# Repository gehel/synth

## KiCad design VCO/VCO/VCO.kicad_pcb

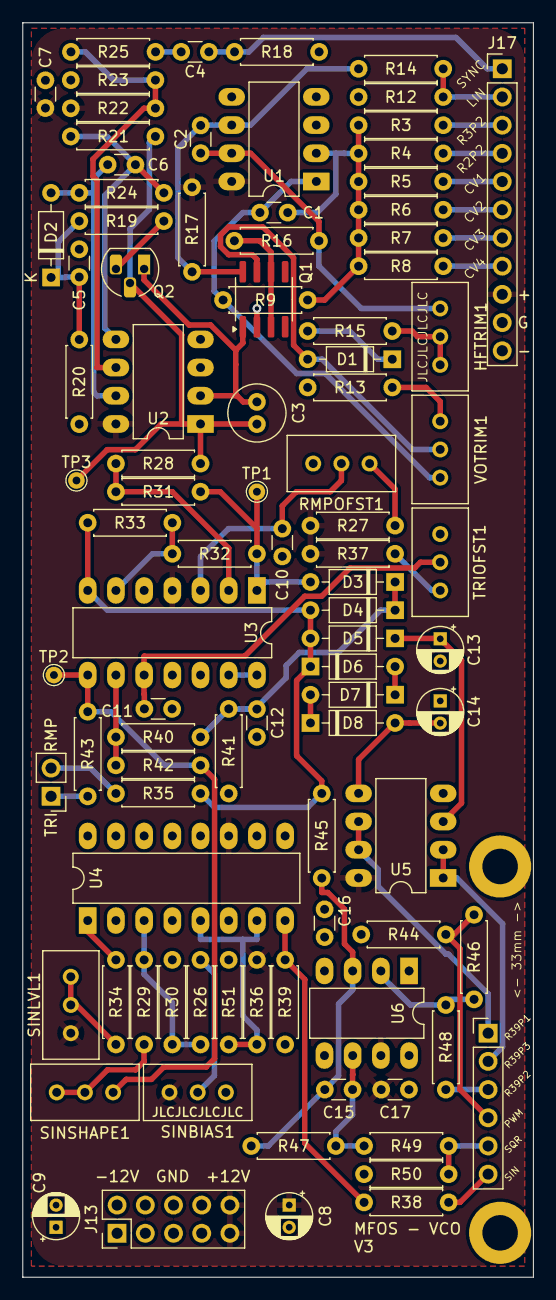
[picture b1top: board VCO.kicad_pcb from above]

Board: 4 copper layers, 46.0 x 113.0 mm, 96 parts (0 on the bottom side), 62 nets.

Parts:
C1, C2, C5: 100pF; C_Disc_D3.0mm_W1.6mm_P2.50mm
C3: 5nF; C_Radial_D5.0mm_H11.0mm_P2.00mm
C4: 1nF; C_Disc_D3.0mm_W1.6mm_P2.50mm
C6: 4.7pF; C_Disc_D3.0mm_W1.6mm_P2.50mm
C7, C10, C11, C16, C17: 100nF; C_Disc_D3.0mm_W1.6mm_P2.50mm
C8, C9: 10uF; CP_Radial_D4.0mm_P2.00mm
C12: 2nF; C_Disc_D3.0mm_W1.6mm_P2.50mm
C13, C14: 1uF; CP_Radial_D4.0mm_P2.00mm
C15: 10pF; C_Disc_D3.0mm_W1.6mm_P2.50mm
D1, D2, D3, D4, D5, D6, D7, D8: 1N914; D_DO-35_SOD27_P7.62mm_Horizontal
H1, H2: MountingHole_Pad; MountingHole_3.2mm_M3_DIN965_Pad
HFTRIM1: 100K; Potentiometer_Bourns_3296W_Vertical
J13: Conn_02x05_Odd_Even; PinHeader_2x05_P2.54mm_Vertical
J15: Conn_01x06; PinHeader_1x06_P2.54mm_Vertical
J17: Conn_01x11; PinHeader_1x11_P2.54mm_Vertical
J19: Conn_01x02; PinHeader_1x02_P2.54mm_Vertical
Q1: SSM2210; SOIC-8_3.9x4.9mm_P1.27mm
Q2: PN4391; TO-92L_HandSolder
R3, R14, R17, R24, R36: 1M; R_Axial_DIN0207_L6.3mm_D2.5mm_P7.62mm_Horizontal
R4, R5, R6, R7, R8, R12, R18, R19, R27, R34, R44, R45: 100K; R_Axial_DIN0207_L6.3mm_D2.5mm_P7.62mm_Horizontal
R9, R23: 2K; R_Axial_DIN0207_L6.3mm_D2.5mm_P7.62mm_Horizontal
R13: 475R; R_Axial_DIN0207_L6.3mm_D2.5mm_P7.62mm_Horizontal
R15, R39, R49: 4.7K; R_Axial_DIN0207_L6.3mm_D2.5mm_P7.62mm_Horizontal
R16, R21, R22, R28, R32, R33, R37, R40, R46, R48: 10K; R_Axial_DIN0207_L6.3mm_D2.5mm_P7.62mm_Horizontal
R20: 18K; R_Axial_DIN0207_L6.3mm_D2.5mm_P7.62mm_Horizontal
R25, R30, R35, R38, R43: 1K; R_Axial_DIN0207_L6.3mm_D2.5mm_P7.62mm_Horizontal
R26: 470K; R_Axial_DIN0207_L6.3mm_D2.5mm_P7.62mm_Horizontal
R29, R41, R42: 20K; R_Axial_DIN0207_L6.3mm_D2.5mm_P7.62mm_Horizontal
R31: 47K; R_Axial_DIN0207_L6.3mm_D2.5mm_P7.62mm_Horizontal
R47: 10M; R_Axial_DIN0207_L6.3mm_D2.5mm_P7.62mm_Horizontal
R50: 3K; R_Axial_DIN0207_L6.3mm_D2.5mm_P7.62mm_Horizontal
R51: 130K; R_Axial_DIN0207_L6.3mm_D2.5mm_P7.62mm_Horizontal
RMPOFST1: 10K; Potentiometer_Bourns_3296W_Vertical
SINBIAS1: 100K; Potentiometer_Bourns_3296W_Vertical
SINLVL1: 1M; Potentiometer_Bourns_3296W_Vertical
SINSHAPE1: 100K; Potentiometer_Bourns_3296W_Vertical
TP1, TP2, TP3: TestPoint; TestPoint_THTPad_D1.5mm_Drill0.7mm
TRIOFST1: 10K; Potentiometer_Bourns_3296W_Vertical
U1: OP275; DIP-8_W7.62mm_LongPads
U2, U5: TL072; DIP-8_W7.62mm_LongPads
U3: TL074; DIP-14_W7.62mm_LongPads
U4: LM13700; DIP-16_W7.62mm_LongPads
U6: TL071; DIP-8_W7.62mm_LongPads
VOTRIM1: 100R; Potentiometer_Bourns_3296W_Vertical

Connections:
+12V: C7.2, C8.1, C17.2, J13.9, J13.10, J17.9, R17.2, R22.2, R27.2, R36.1, R37.2, SINBIAS1.3, SINLVL1.3, U1.8 (V+), U2.8 (V+), U3.4 (V+), U4.11 (V+), U5.8 (V+), U6.7 (V+)
-12V: C9.2, C12.1, C16.2, J13.1, J13.2, J17.11, R20.1, R39.2, R41.2, SINBIAS1.1, U1.4 (V-), U2.4 (V-), U3.11 (V-), U4.6 (V-), U5.4 (V-), U6.4 (V-)
CV1: J17.5, R5.1
CV2: J17.6, R6.1
CV3: J17.7, R7.1
CV4: J17.8, R8.1
GND: C5.1, C7.1, C8.2, C9.1, C10.1, C11.1, C13.2, C14.1, C16.1, C17.1, H1.1, H2.1, J13.3, J13.4, J13.5, J13.6, J13.7, J13.8, J17.10, Q1.2 (B1), R12.1, R13.1, R18.1, R23.2, R30.2, R44.2, R50.2, R51.2, RMPOFST1.1, TRIOFST1.1, U1.3 (+), U1.5 (+), U2.3 (+), U3.5 (+), U3.12 (+), U4.4 (-), U4.13 (-), U4.14 (+)
LIN: J17.2, R12.2, R14.1
unnamed: C1.2, R9.2, U1.1, VOTRIM1.1
unnamed: C2.2, HFTRIM1.3, R16.2, U1.7
unnamed: C4.2, R25.1
unnamed: C15.1, R47.2, R49.1, U6.6
unnamed: D1.2 (A), Q1.7 (B2), VOTRIM1.2
unnamed: D1.1 (K), R15.1
unnamed: C6.2, D2.2 (A), R24.2, U2.7
unnamed: C5.2, D2.1 (K), R19.2, R20.2
unnamed: D3.2 (A), R31.2, R32.2, TP1.1, U3.1
unnamed: C12.2, D3.1 (K), D4.1 (K), R40.1, R41.1
unnamed: D4.2 (A), D5.2 (A), D6.1 (K), R33.2, R35.1, R45.1, U3.7
unnamed: C13.1, D5.1 (K), U5.3 (+)
unnamed: D6.2 (A), D7.1 (K)
unnamed: D7.2 (A), D8.1 (K)
unnamed: C14.2, D8.2 (A), U5.5 (+)
unnamed: HFTRIM1.1, HFTRIM1.2, R15.2
unnamed: C3.1, Q1.1 (C1), Q2.1 (D), U2.2 (-)
unnamed: Q1.3 (E1), Q1.6 (E2), R16.1
unnamed: C2.1, Q1.8 (C2), R14.2, R17.1, U1.6 (-)
unnamed: Q2.3 (G), R19.1
unnamed: R13.2, VOTRIM1.3
unnamed: R26.1, SINBIAS1.2
unnamed: R27.1, RMPOFST1.3
unnamed: R29.1, SINSHAPE1.1, SINSHAPE1.2
unnamed: R34.1, SINLVL1.1, SINLVL1.2
unnamed: R34.2, U4.1
unnamed: R36.2, R51.1, U4.5, U4.7
unnamed: R37.1, TRIOFST1.3
unnamed: R38.1, R39.1, U4.8
unnamed: R42.2, R43.1, SINSHAPE1.3, TP2.1, U3.8
unnamed: C1.1, R3.2, R4.2, R5.2, R6.2, R7.2, R8.2, R9.1, U1.2 (-)
unnamed: C6.1, R21.2, R24.1, U2.5 (+)
unnamed: R22.1, R23.1, R25.2, U2.6 (-)
unnamed: C10.2, RMPOFST1.2, U3.3 (+)
unnamed: R28.2, R31.1, U3.2 (-)
unnamed: R32.1, R33.1, U3.6 (-)
unnamed: C11.2, TRIOFST1.2, U3.10 (+)
unnamed: R40.2, R42.1, U3.9 (-)
unnamed: U3.13 (-), U3.14
unnamed: R26.2, R29.2, R30.1, U4.3 (+)
unnamed: C15.2, R45.2, R47.1, U6.3 (+)
unnamed: R46.2, R48.1, U6.2 (-)
PWM: J15.4, R44.1, R46.1
R2P2: J17.4, R4.1
R3P2: J17.3, R3.1
R39P1: J15.1, U5.6 (-), U5.7
R39P2: J15.3, R48.2
R39P3: J15.2, U5.1, U5.2 (-)
RAW: C3.2, Q2.2 (S), R21.1, R28.1, TP3.1, U2.1
RMP: J19.2, R35.2
SIN: J15.6, R38.2
SQR: J15.5, R49.2, R50.1
SYNC: C4.1, J17.1, R18.2
TRI: J19.1, R43.2

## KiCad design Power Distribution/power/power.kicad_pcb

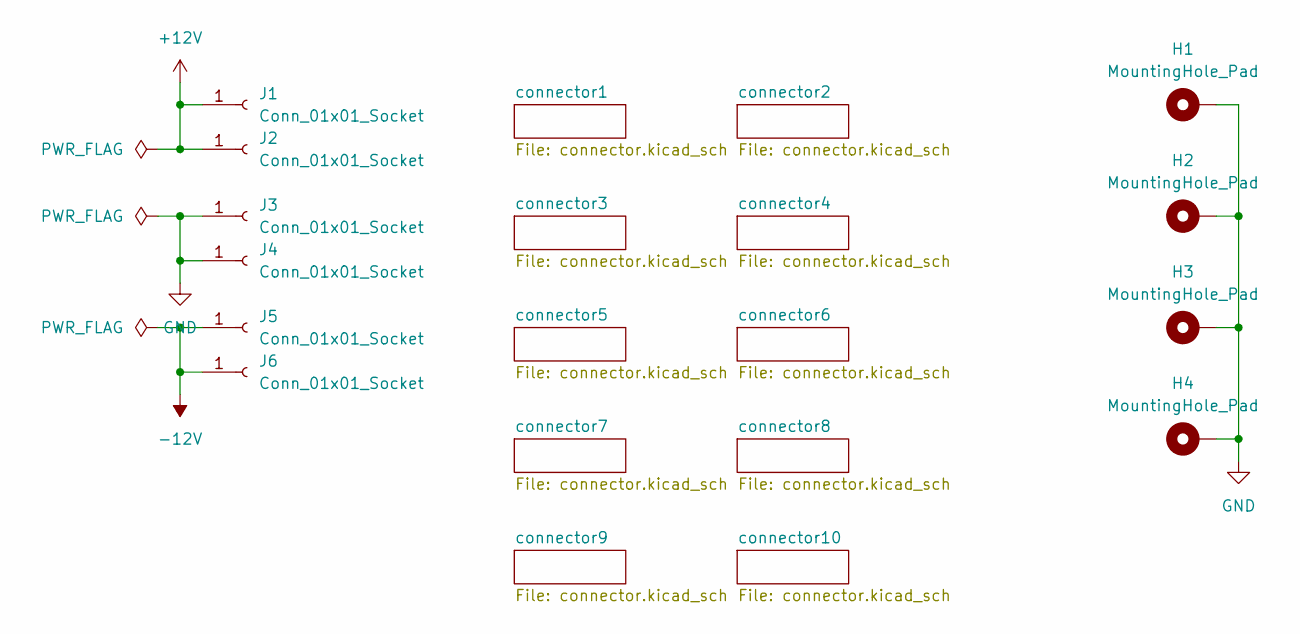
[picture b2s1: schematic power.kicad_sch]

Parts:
H1, H2, H3, H4: MountingHole_Pad; MountingHole_3.2mm_M3_Pad
J1, J2, J3, J4, J5, J6: Conn_01x01_Socket; Pin_D1.0mm_L10.0mm

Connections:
+12V: J1.1, J2.1; also elsewhere on the board
-12V: J5.1, J6.1; also elsewhere on the board
GND: H1.1, H2.1, H3.1, H4.1, J3.1, J4.1; also elsewhere on the board

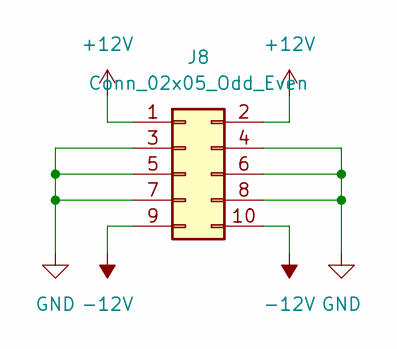
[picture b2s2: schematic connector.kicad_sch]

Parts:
J8: Conn_02x05_Odd_Even; IDC-Header_2x05_P2.54mm_Vertical

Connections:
+12V: J8.1, J8.2; also elsewhere on the board
-12V: J8.9, J8.10; also elsewhere on the board
GND: J8.3, J8.4, J8.5, J8.6, J8.7, J8.8; also elsewhere on the board

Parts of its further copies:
J7, J9, J10, J11, J12, J13, J14, J15, J16: Conn_02x05_Odd_Even; IDC-Header_2x05_P2.54mm_Vertical

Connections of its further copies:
+12V: J7.1, J7.2, J9.1, J9.2, J10.1, J10.2, J11.1, J11.2, J12.1, J12.2, J13.1, J13.2, J14.1, J14.2, J15.1, J15.2, J16.1, J16.2; also elsewhere on the board
-12V: J7.9, J7.10, J9.9, J9.10, J10.9, J10.10, J11.9, J11.10, J12.9, J12.10, J13.9, J13.10, J14.9, J14.10, J15.9, J15.10, J16.9, J16.10; also elsewhere on the board
GND: J7.3, J7.4, J7.5, J7.6, J7.7, J7.8, J9.3, J9.4, J9.5, J9.6, J9.7, J9.8, J10.3, J10.4, J10.5, J10.6, J10.7, J10.8, J11.3, J11.4, J11.5, J11.6, J11.7, J11.8, J12.3, J12.4, J12.5, J12.6, J12.7, J12.8, J13.3, J13.4, J13.5, J13.6, J13.7, J13.8, J14.3, J14.4, J14.5, J14.6, J14.7, J14.8, J15.3, J15.4, J15.5, J15.6, J15.7, J15.8, J16.3, J16.4, J16.5, J16.6, J16.7, J16.8; also elsewhere on the board

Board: 2 copper layers, 20 parts (0 on the bottom side), 3 nets, no tracks yet.

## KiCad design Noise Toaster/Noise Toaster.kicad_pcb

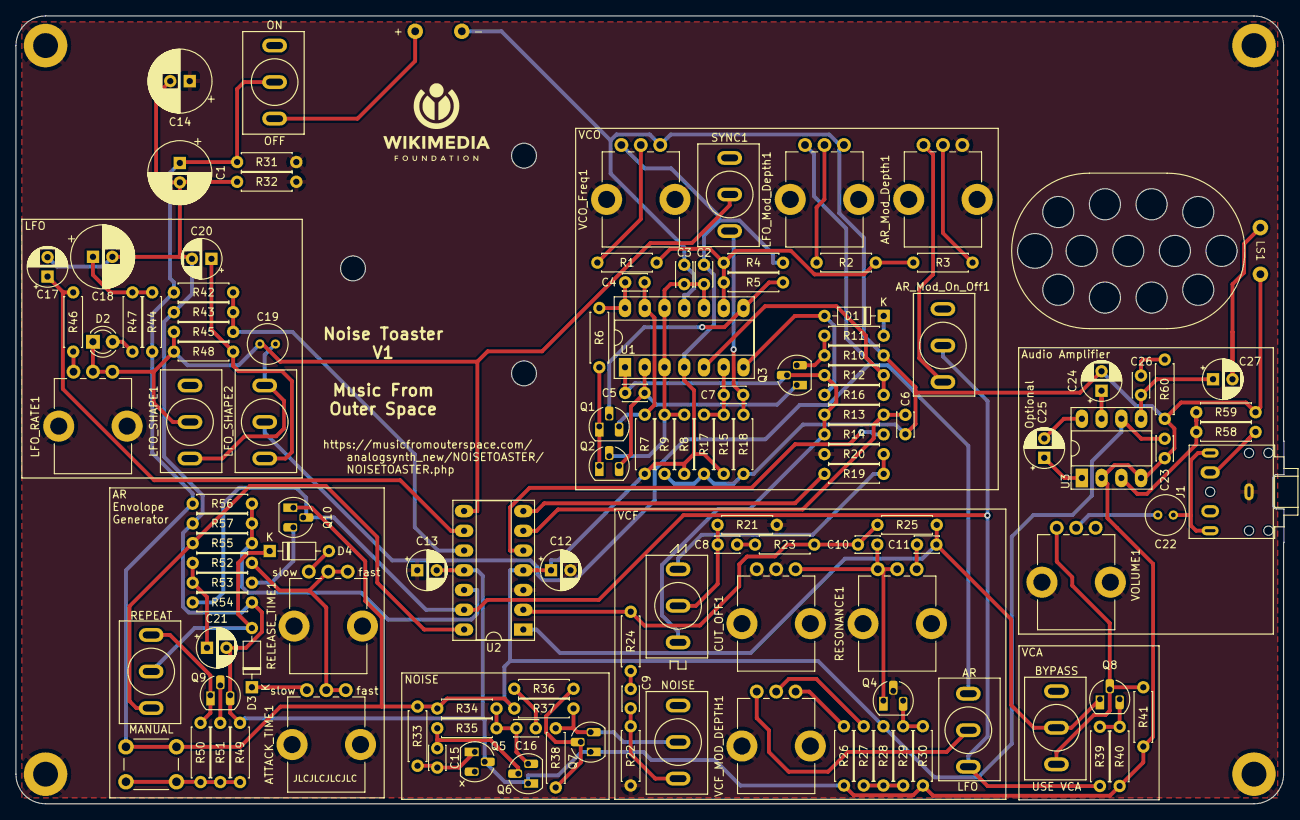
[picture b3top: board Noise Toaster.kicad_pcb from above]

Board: 2 copper layers, 163.1 x 101.3 mm, 132 parts (0 on the bottom side), 78 nets.

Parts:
AR_Mod_Depth1: 100K; Potentiometer_Bourns_PTV09A-1_Single_Vertical
AR_Mod_On_Off1, AR_Mod_On_Off2: SW_SPDT; ToggleSwitch_MTS-102_SPDT
ATTACK_TIME1: 1M; Potentiometer_Bourns_PTV09A-1_Single_Vertical
BT1: Battery; Battery holder 9v
C1, C14, C18: 470uF; CP_Radial_D8.0mm_P2.50mm
C2, C3, C6, C8, C9, C15, C16, C23, C26: 100nF; C_Disc_D3.0mm_W2.0mm_P2.50mm
C4: 100pF; C_Disc_D3.0mm_W2.0mm_P2.50mm
C5, C10, C11: 1nF; C_Disc_D3.0mm_W2.0mm_P2.50mm
C7: 10nF; C_Disc_D3.0mm_W2.0mm_P2.50mm
C12, C13, C24, C25: 10uF; CP_Radial_D5.0mm_P2.50mm
C17, C20: 1uF; CP_Radial_D5.0mm_P2.50mm
C19, C22: 1uF; C_Radial_D5.0mm_H7.0mm_P2.00mm
C21: 4.7uF; CP_Radial_D5.0mm_P2.50mm
C27: 220uF; CP_Radial_D5.0mm_P2.50mm
CUT_OFF1: 100K; Potentiometer_Bourns_PTV09A-1_Single_Vertical
D1, D3, D4: 1N914; D_DO-35_SOD27_P7.62mm_Horizontal
D2: LED; LED_D3.0mm
H1, H2, H3, H4: MountingHole_Pad; MountingHole_3.2mm_M3_DIN965_Pad
J1: AudioJack3_SwitchTR; Jack_3.5mm_CUI_SJ1-3525N_Horizontal
LFO_Mod_Depth1: 100K; Potentiometer_Bourns_PTV09A-1_Single_Vertical
LFO_RATE1: 1M; Potentiometer_Bourns_PTV09A-1_Single_Vertical
LFO_SHAPE1, LFO_SHAPE2: SW_SPDT; ToggleSwitch_MTS-102_SPDT
LS1: Speaker; Speaker 2030
MANUAL_GATE1: SW_Push; SW_PUSH_6mm
MANUAL_REPEAT1: SW_SPDT; ToggleSwitch_MTS-102_SPDT
NOISE_TO_VCF1: SW_SPDT; ToggleSwitch_MTS-102_SPDT
Q1, Q2, Q5, Q6, Q7: 2N3904; TO-92_HandSolder
Q3, Q4, Q8, Q10: 2N5457; TO-92_HandSolder
Q9: 2N3906; TO-92_HandSolder
R1, R48: 75K; R_Axial_DIN0207_L6.3mm_D2.5mm_P7.62mm_Horizontal
R2, R18, R19, R28, R30, R36, R41, R42, R43, R45, R55, R58: 100K; R_Axial_DIN0207_L6.3mm_D2.5mm_P7.62mm_Horizontal
R3: 36K; R_Axial_DIN0207_L6.3mm_D2.5mm_P7.62mm_Horizontal
R4: 270K; R_Axial_DIN0207_L6.3mm_D2.5mm_P7.62mm_Horizontal
R5: 2K; R_Axial_DIN0207_L6.3mm_D2.5mm_P7.62mm_Horizontal
R6, R11, R12, R14, R15, R20, R34, R37, R49, R51, R53: 10K; R_Axial_DIN0207_L6.3mm_D2.5mm_P7.62mm_Horizontal
R7, R10, R13: 2M; R_Axial_DIN0207_L6.3mm_D2.5mm_P7.62mm_Horizontal
R8, R9, R31, R32, R54: 4.7K; R_Axial_DIN0207_L6.3mm_D2.5mm_P7.62mm_Horizontal
R16: 300K; R_Axial_DIN0207_L6.3mm_D2.5mm_P7.62mm_Horizontal
R17: 15K; R_Axial_DIN0207_L6.3mm_D2.5mm_P7.62mm_Horizontal
R21, R22: 47K; R_Axial_DIN0207_L6.3mm_D2.5mm_P7.62mm_Horizontal
R23, R25: 4.7M; R_Axial_DIN0207_L6.3mm_D2.5mm_P7.62mm_Horizontal
R24: 3M; R_Axial_DIN0207_L6.3mm_D2.5mm_P7.62mm_Horizontal
R26: 27K; R_Axial_DIN0207_L6.3mm_D2.5mm_P7.62mm_Horizontal
R27, R29: 39K; R_Axial_DIN0207_L6.3mm_D2.5mm_P7.62mm_Horizontal
R33, R40: 1M; R_Axial_DIN0207_L6.3mm_D2.5mm_P7.62mm_Horizontal
R35, R38, R39: 470K; R_Axial_DIN0207_L6.3mm_D2.5mm_P7.62mm_Horizontal
R44, R46, R47: 3K; R_Axial_DIN0207_L6.3mm_D2.5mm_P7.62mm_Horizontal
R50: 200R; R_Axial_DIN0207_L6.3mm_D2.5mm_P7.62mm_Horizontal
R52: 820R; R_Axial_DIN0207_L6.3mm_D2.5mm_P7.62mm_Horizontal
R56, R57: 150K; R_Axial_DIN0207_L6.3mm_D2.5mm_P7.62mm_Horizontal
R59: 20K; R_Axial_DIN0207_L6.3mm_D2.5mm_P7.62mm_Horizontal
R60: 10R; R_Axial_DIN0207_L6.3mm_D2.5mm_P7.62mm_Horizontal
RELEASE_TIME1: 1M; Potentiometer_Bourns_PTV09A-1_Single_Vertical
RESONANCE1: 100K; Potentiometer_Bourns_PTV09A-1_Single_Vertical
SYNC1: SW_SPDT; ToggleSwitch_MTS-102_SPDT
U1, U2: LM324; DIP-14_W7.62mm_Socket_LongPads
U3: LM386; DIP-8_W7.62mm_Socket_LongPads
VCA_BYPASS1: SW_SPDT; ToggleSwitch_MTS-102_SPDT
VCF_MOD_DEPTH1: 100K; Potentiometer_Bourns_PTV09A-1_Single_Vertical
VCF_MOD_SRC1: SW_SPDT_MSM; ToggleSwitch_MTS-102_SPDT
VCO_Freq1: 100K; Potentiometer_Bourns_PTV09A-1_Single_Vertical
VCO_TO_VCF1: SW_SPDT_MSM; ToggleSwitch_MTS-102_SPDT
VOLUME1: 100K; Potentiometer_Bourns_PTV09A-1_Single_Vertical

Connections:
AGR: AR_Mod_On_Off1.2 (B), Q10.2 (S), R39.2, R54.2, U2.13 (-), VCF_MOD_SRC1.3
AUDIO_OUT: Q8.2 (S), R41.2, VCA_BYPASS1.1 (A), VOLUME1.1
BN: BT1.2 (-), C1.2, C3.1, C6.1, C13.2, C14.2, C17.2, C18.2, C20.2, C21.2, C23.2, C24.2, LFO_Mod_Depth1.3, LS1.2, Q5.2 (B), Q6.1 (E), Q7.1 (E), Q9.3 (C), R9.2, R10.2, R17.2, R18.2, R26.1, R30.1, R32.1, R40.1, R41.1, R43.1, R49.1, R54.1, R57.1, R59.1, R60.1, U1.11 (V-), U2.11 (V-), U3.2 (-), U3.4 (GND), VCO_Freq1.3, VOLUME1.3
BP: AR_Mod_On_Off2.2 (B), C1.1, C2.1, C12.1, C23.1, MANUAL_GATE1.1, Q10.1 (D), R4.2, R7.1, R8.2, R15.1, R28.2, R31.2, R33.1, R34.1, R37.1, R42.2, R44.2, R56.2, U1.4 (V+), U2.4 (V+), U3.6 (V+), VCO_Freq1.1
GND: AR_Mod_Depth1.3, AR_Mod_Depth1.MP (MountPin), ATTACK_TIME1.MP (MountPin), C12.2, C13.1, C14.1, CUT_OFF1.1, CUT_OFF1.2, CUT_OFF1.MP (MountPin), H1.1, H2.1, H3.1, H4.1, J1.S, LFO_Mod_Depth1.MP (MountPin), LFO_RATE1.MP (MountPin), Q4.2 (S), R20.2, R21.2, R22.2, R31.1, R32.2, RELEASE_TIME1.MP (MountPin), RESONANCE1.MP (MountPin), U2.3 (+), VCF_MOD_DEPTH1.MP (MountPin), VCO_Freq1.MP (MountPin), VOLUME1.MP (MountPin)
LFO: LFO_Mod_Depth1.1, LFO_SHAPE2.2 (B), VCF_MOD_SRC1.1
NOISE: NOISE_TO_VCF1.2 (B), Q7.3 (C), R37.2, R38.1
unnamed: AR_Mod_Depth1.2, R3.1
unnamed: AR_Mod_Depth1.1, AR_Mod_On_Off1.3 (C)
unnamed: AR_Mod_On_Off2.1 (A), BT1.1 (+)
unnamed: ATTACK_TIME1.2, ATTACK_TIME1.3, R52.1, RELEASE_TIME1.2, RELEASE_TIME1.3
unnamed: C4.2, R6.1, U1.14
unnamed: C8.1, R21.1, VCO_TO_VCF1.2
unnamed: C8.2, R23.1
unnamed: C9.2, R24.1
unnamed: C11.1, RESONANCE1.3
unnamed: C16.1, R36.1
unnamed: C18.1, R44.1, R47.1
unnamed: C21.1, R52.2, R53.1
unnamed: C22.1, J1.R, J1.T
unnamed: C22.2, VOLUME1.2
unnamed: C25.1, U3.1 (GAIN)
unnamed: C25.2, U3.8 (GAIN)
unnamed: C26.1, C27.1, U3.5
unnamed: C26.2, R60.2
unnamed: C27.2, LS1.1
unnamed: D1.2 (A), R16.2, U1.7
unnamed: D1.1 (K), R11.2
unnamed: D2.2 (A), R47.2
unnamed: D3.2 (A), D4.1 (K), MANUAL_REPEAT1.2 (B)
unnamed: ATTACK_TIME1.1, D3.1 (K)
unnamed: D4.2 (A), RELEASE_TIME1.1
unnamed: J1.TN, R58.2
unnamed: LFO_Mod_Depth1.2, R2.1
unnamed: LFO_RATE1.1, R46.2
unnamed: C19.1, LFO_SHAPE1.3 (C), LFO_SHAPE2.1 (A)
unnamed: C20.1, LFO_SHAPE2.3 (C), R48.1
unnamed: MANUAL_GATE1.2, R49.2, R50.1, R51.1
unnamed: MANUAL_REPEAT1.1 (A), R55.2, U2.14
unnamed: MANUAL_REPEAT1.3 (C), Q9.1 (E), R50.2
unnamed: C9.1, NOISE_TO_VCF1.1 (A), R22.1
unnamed: Q1.2 (B), R5.2, U1.8
unnamed: C4.1, Q1.3 (C), R7.2, U1.13 (-)
unnamed: Q1.1 (E), Q2.1 (E), R6.2
unnamed: C2.2, C3.2, Q2.2 (B), R8.1, R9.1, U1.3 (+), U1.10 (+), U1.12 (+)
unnamed: C5.1, Q2.3 (C), Q3.1 (D), U1.2 (-)
unnamed: Q3.3 (G), R10.1, R11.1
unnamed: C10.2, CUT_OFF1.3, Q4.1 (D), RESONANCE1.1, RESONANCE1.2
unnamed: Q4.3 (G), R29.2, R30.2
unnamed: C15.2, Q5.1 (E), R33.2
unnamed: C15.1, Q6.2 (B), R35.2
unnamed: C16.2, Q6.3 (C), R34.2, R35.1
unnamed: Q7.2 (B), R36.2, R38.2
unnamed: Q8.3 (G), R39.1, R40.2
unnamed: Q9.2 (B), R51.2
unnamed: Q10.3 (G), R53.2
unnamed: R1.1, VCO_Freq1.2
unnamed: R19.1, U2.7
unnamed: R26.2, VCF_MOD_DEPTH1.3
unnamed: R27.1, VCF_MOD_DEPTH1.2
unnamed: R27.2, R28.1, R29.1
unnamed: C7.1, R18.1, SYNC1.1 (A)
unnamed: R12.2, R16.1, U1.5 (+)
unnamed: C7.2, R15.2, R17.1, U1.6 (-)
unnamed: R1.2, R2.2, R3.2, R4.1, R5.1, U1.9 (-)
unnamed: C10.1, R23.2, R24.2, R25.1, U2.2 (-)
unnamed: R14.2, U2.5 (+)
unnamed: C6.2, R13.2, U2.6 (-)
unnamed: R42.1, R43.2, R45.2, U2.10 (+)
unnamed: C17.1, R46.1, U2.9 (-)
unnamed: R55.1, R56.1, R57.2, U2.12 (+)
unnamed: R58.1, R59.2, U3.3 (+)
unnamed: C24.1, U3.7 (BYPASS)
unnamed: VCF_MOD_DEPTH1.1, VCF_MOD_SRC1.2
RMP: C5.2, Q3.2 (S), R12.1, R13.1, R14.1, U1.1, VCO_TO_VCF1.1
SQR: R19.2, R20.1, VCO_TO_VCF1.3
SYNC: C19.2, D2.1 (K), LFO_RATE1.2, LFO_RATE1.3, LFO_SHAPE1.2 (B), R45.1, R48.2, SYNC1.2 (B), U2.8
VCF_TO_VCA: C11.2, Q8.1 (D), R25.2, U2.1, VCA_BYPASS1.2 (B)

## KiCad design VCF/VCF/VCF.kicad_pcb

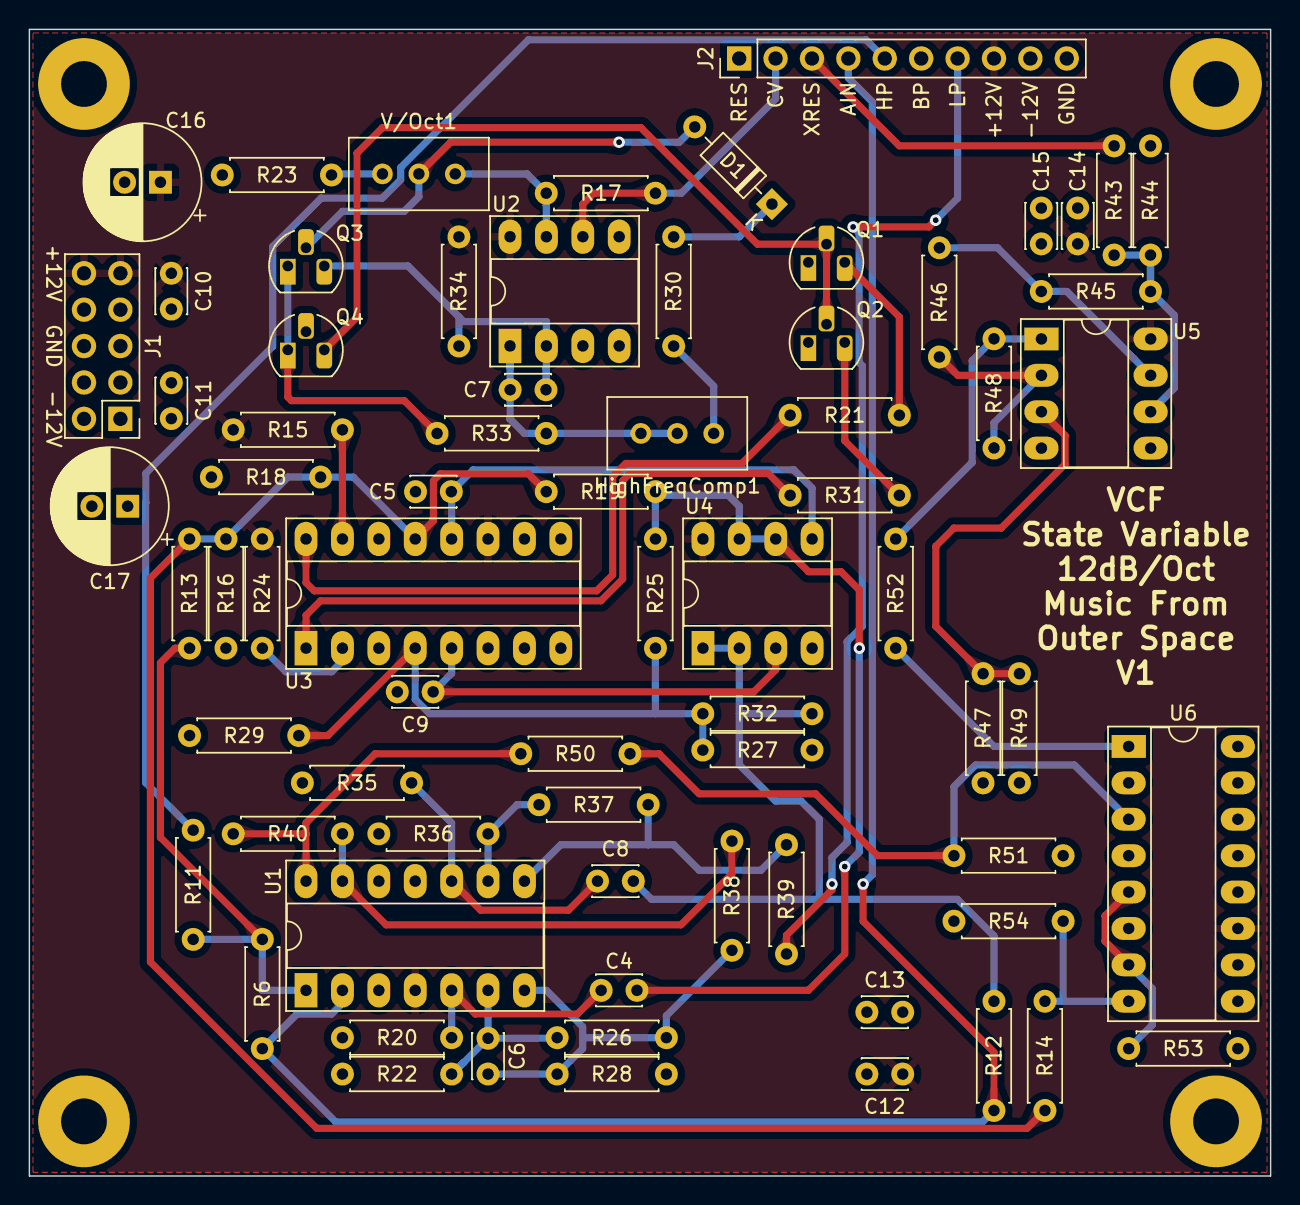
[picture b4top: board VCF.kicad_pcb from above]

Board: 4 copper layers, 86.6 x 80.0 mm, 76 parts (0 on the bottom side), 49 nets.

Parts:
C4, C8, C10, C11, C12, C13, C14, C15: 100nF; C_Disc_D3.0mm_W2.0mm_P2.50mm
C5, C9: 220pF; C_Disc_D3.0mm_W2.0mm_P2.50mm
C6: 22pF; C_Disc_D3.0mm_W2.0mm_P2.50mm
C7: 1nF; C_Disc_D3.0mm_W2.0mm_P2.50mm
C16, C17: 10uF; CP_Radial_D8.0mm_P2.50mm
D1: 1N914; D_DO-35_SOD27_P7.62mm_Horizontal
H1, H2, H3, H4: MountingHole_Pad; MountingHole_3.2mm_M3_Pad
HighFreqComp1: 2K; Potentiometer_Bourns_3296W_Vertical
J1: Conn_02x05_Odd_Even; PinHeader_2x05_P2.54mm_Vertical
J2: Conn_01x10; PinHeader_1x10_P2.54mm_Vertical
Q1, Q2: 2N3906; TO-92_HandSolder
Q3, Q4: 2N3904; TO-92_HandSolder
R6: 300K; R_Axial_DIN0207_L6.3mm_D2.5mm_P7.62mm_Horizontal
R11, R13, R19, R25, R32, R43, R44, R46, R47, R48: 100K; R_Axial_DIN0207_L6.3mm_D2.5mm_P7.62mm_Horizontal
R12, R38: 49.9K; R_Axial_DIN0207_L6.3mm_D2.5mm_P7.62mm_Horizontal
R14, R26, R37, R40: 150K; R_Axial_DIN0207_L6.3mm_D2.5mm_P7.62mm_Horizontal
R15, R24: 20K; R_Axial_DIN0207_L6.3mm_D2.5mm_P7.62mm_Horizontal
R16: 43K; R_Axial_DIN0207_L6.3mm_D2.5mm_P7.62mm_Horizontal
R17, R28, R39: 2K; R_Axial_DIN0207_L6.3mm_D2.5mm_P7.62mm_Horizontal
R18, R29, R51: 100R; R_Axial_DIN0207_L6.3mm_D2.5mm_P7.62mm_Horizontal
R20, R35: 4.7M; R_Axial_DIN0207_L6.3mm_D2.5mm_P7.62mm_Horizontal
R21, R31: 7.5K; R_Axial_DIN0207_L6.3mm_D2.5mm_P7.62mm_Horizontal
R22: 180K; R_Axial_DIN0207_L6.3mm_D2.5mm_P7.62mm_Horizontal
R23: 475R; R_Axial_DIN0207_L6.3mm_D2.5mm_P7.62mm_Horizontal
R27, R36: 39K; R_Axial_DIN0207_L6.3mm_D2.5mm_P7.62mm_Horizontal
R30, R33: 10K; R_Axial_DIN0207_L6.3mm_D2.5mm_P7.62mm_Horizontal
R34: 1M; R_Axial_DIN0207_L6.3mm_D2.5mm_P7.62mm_Horizontal
R45: 120K; R_Axial_DIN0207_L6.3mm_D2.5mm_P7.62mm_Horizontal
R49, R50, R52, R53: 30K; R_Axial_DIN0207_L6.3mm_D2.5mm_P7.62mm_Horizontal
R54: 4.7K; R_Axial_DIN0207_L6.3mm_D2.5mm_P7.62mm_Horizontal
U1: TL074; DIP-14_W7.62mm_Socket_LongPads
U2, U4, U5: TL072; DIP-8_W7.62mm_Socket_LongPads
U3, U6: LM13700; DIP-16_W7.62mm_Socket_LongPads
V/Oct1: 100R; Potentiometer_Bourns_3296W_Vertical

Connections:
+12V: C10.1, C12.1, C14.1, C16.1, J1.9, J1.10, J2.8, R15.1, R24.1, R34.1, U1.4 (V+), U2.8 (V+), U3.11 (V+), U4.8 (V+), U5.8 (V+), U6.11 (V+)
-12V: C11.2, C13.2, C15.2, C17.2, J1.1, J1.2, J2.9, R16.1, R27.1, R47.1, R54.1, U1.11 (V-), U2.4 (V-), U3.6 (V-), U4.4 (V-), U5.4 (V-), U6.6 (V-)
AIN: J2.4, R6.1, R12.1, U1.2 (-)
BP: J2.6, R28.2
CV/CO: J2.2, R17.1, U2.6 (-)
GND: C5.1, C9.1, C10.2, C11.1, C12.2, C13.1, C14.2, C15.1, C16.2, C17.1, H1.1, H2.1, H3.1, H4.1, J1.3, J1.4, J1.5, J1.6, J1.7, J1.8, J2.10, Q1.1 (E), Q2.1 (E), Q4.2 (B), R18.1, R20.1, R22.1, R23.2, R29.1, R35.1, R36.1, R49.2, R51.1, R53.1, U1.3 (+), U1.12 (+), U2.3 (+), U2.5 (+), U3.3 (+), U3.14 (+), U5.5 (+), U6.4 (-), U6.13 (-), U6.14 (+)
HP: J2.5, R11.2
LP: J2.7, R39.2
unnamed: C6.1, R26.2, R28.1, R38.1, U1.7
unnamed: C7.2, HighFreqComp1.1, HighFreqComp1.2, R33.1, U2.1
unnamed: D1.2 (A), Q3.2 (B), V/Oct1.2
unnamed: D1.1 (K), R30.1
unnamed: HighFreqComp1.3, R30.2
unnamed: Q1.2 (B), Q2.2 (B), Q4.3 (C)
unnamed: Q1.3 (C), R21.1
unnamed: Q2.3 (C), R31.1
unnamed: C7.1, Q3.3 (C), R34.2, U2.2 (-)
unnamed: Q3.1 (E), Q4.1 (E), R33.2
unnamed: R6.2, R11.1, R13.1, U1.1
unnamed: R17.2, U2.7, V/Oct1.1
unnamed: R21.2, U3.16
unnamed: R23.1, V/Oct1.3
unnamed: R31.2, U3.1
unnamed: R37.2, R39.1, U1.8
unnamed: R45.2, R46.1, U5.7
unnamed: R48.2, R52.1, U5.1
unnamed: R52.2, U6.1
unnamed: R53.2, U6.5, U6.7
unnamed: C4.2, R20.2, U1.5 (+)
unnamed: C6.2, R22.2, R26.1, U1.6 (-)
unnamed: C8.1, R35.2, U1.10 (+)
unnamed: R36.2, R37.1, U1.9 (-)
unnamed: R38.2, R40.1, U1.13 (-)
unnamed: R13.2, R14.2, R16.2, R18.2, R19.1, U3.13 (-)
unnamed: R15.2, U3.15 (DIODE_BIAS)
unnamed: R25.2, R27.2, R29.2, R32.1, U3.4 (-)
unnamed: R24.2, U3.2 (DIODE_BIAS)
unnamed: C9.2, U3.5, U4.3 (+)
unnamed: C8.2, R12.2, R32.2, U4.1, U4.2 (-)
unnamed: C5.2, U3.12, U4.5 (+)
unnamed: C4.1, R19.2, R25.1, U4.6 (-), U4.7
unnamed: R47.2, R49.1, U5.3 (+)
unnamed: R46.2, R48.1, U5.2 (-)
unnamed: R43.2, R44.2, R45.1, U5.6 (-)
unnamed: R50.2, R51.2, U6.3 (+)
RA: R40.2, R50.1, U1.14
RB: R14.1, R54.2, U6.8
RES: J2.1, R44.1
XRES: J2.3, R43.1

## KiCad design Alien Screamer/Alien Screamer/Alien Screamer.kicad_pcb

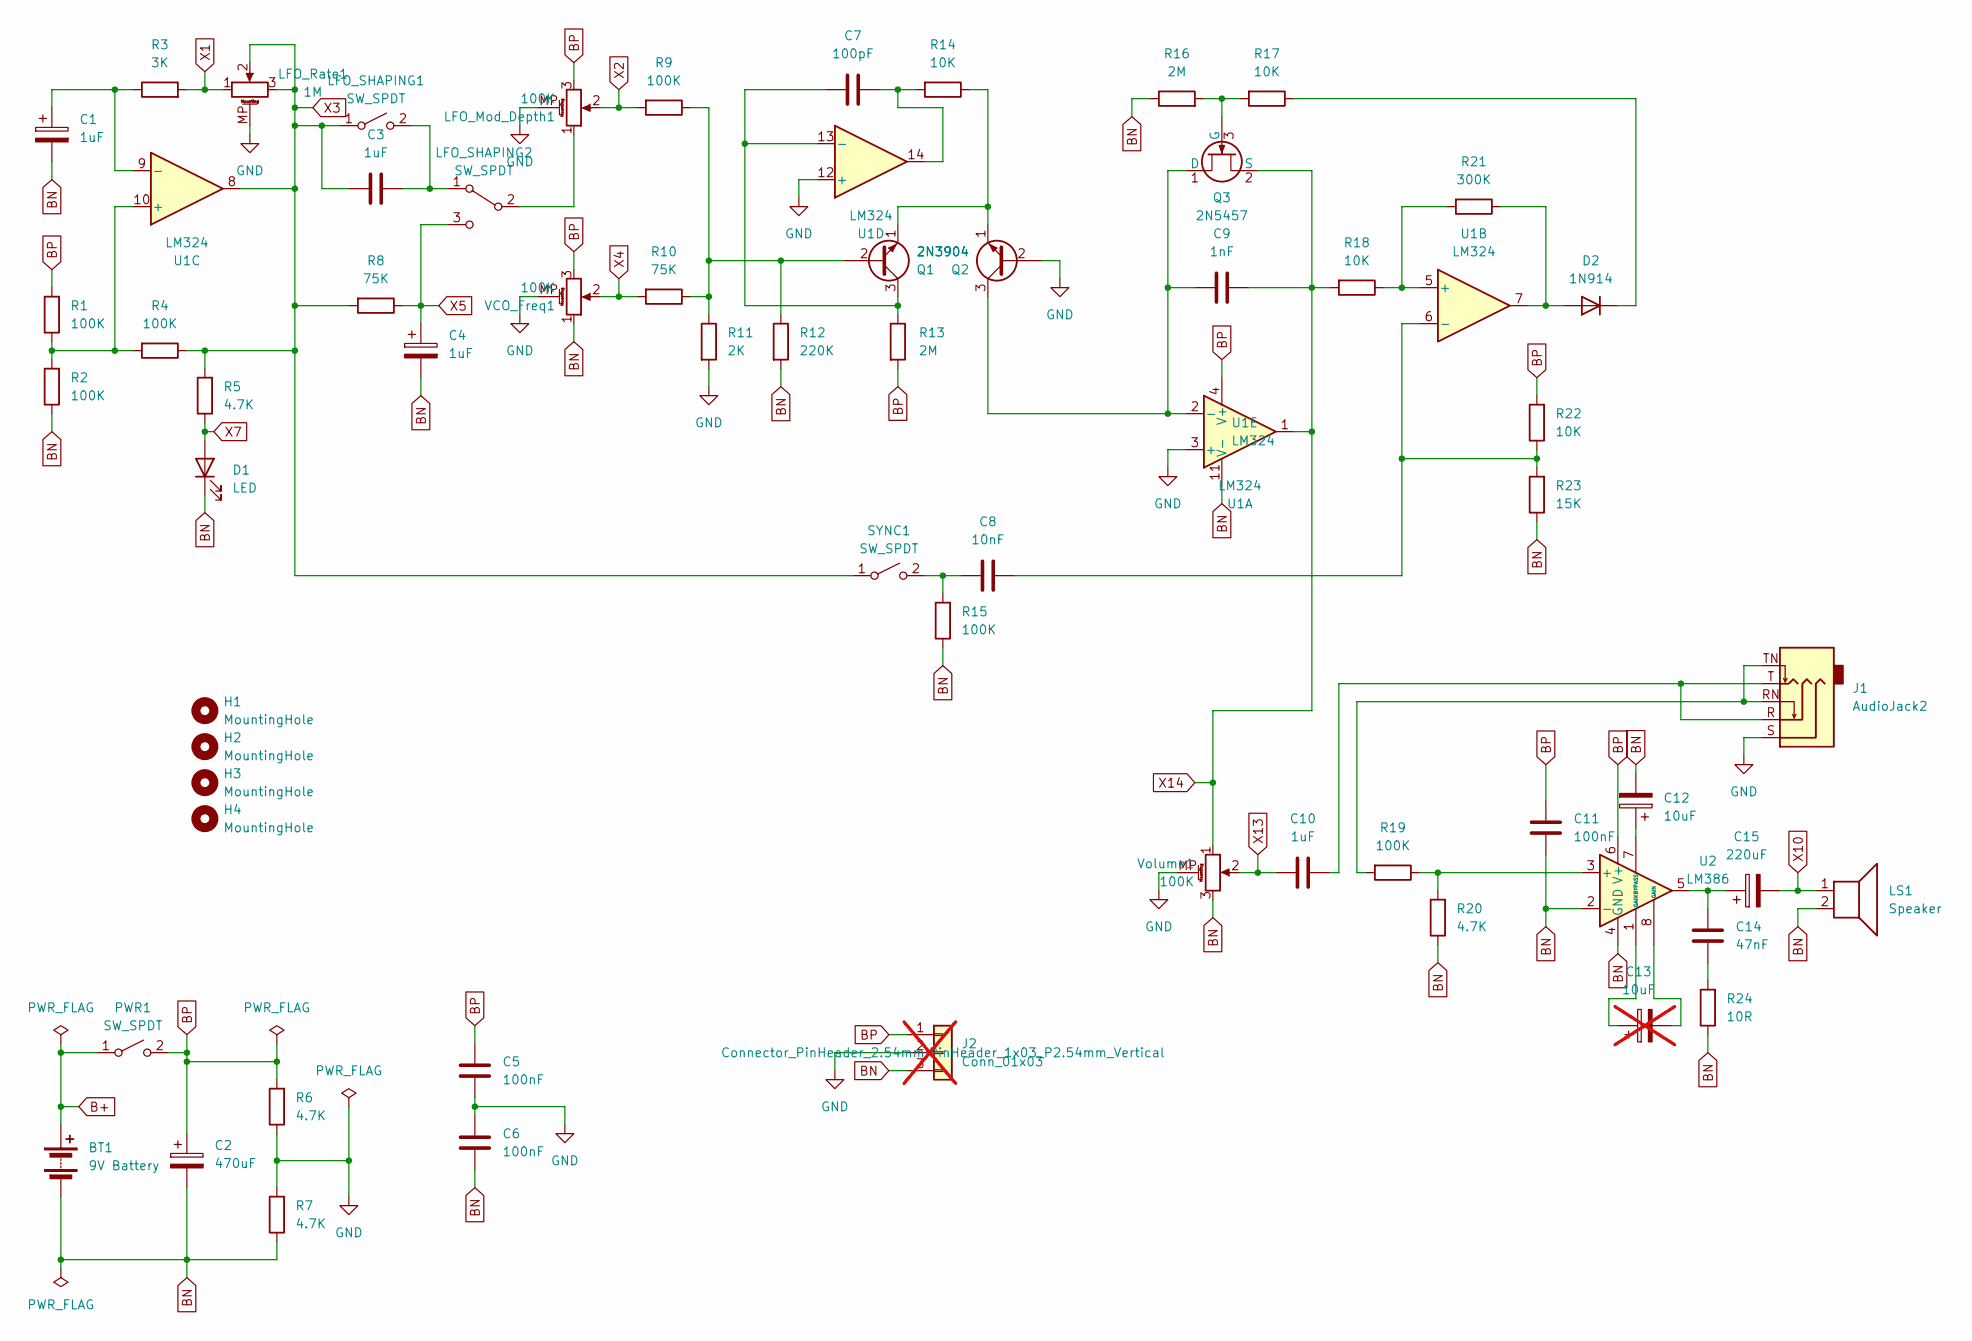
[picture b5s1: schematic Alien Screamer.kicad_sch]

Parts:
BT1: 9V Battery; Battery holder 9v
C1, C4: 1uF; CP_Radial_D5.0mm_P2.00mm
C2: 470uF; CP_Radial_D8.0mm_P3.80mm
C3, C10: 1uF; C_Radial_D5.0mm_H5.0mm_P2.00mm
C5, C6, C11: 100nF; C_Disc_D3.0mm_W1.6mm_P2.50mm
C7: 100pF; C_Disc_D3.0mm_W1.6mm_P2.50mm
C8: 10nF; C_Disc_D3.0mm_W1.6mm_P2.50mm
C9: 1nF; C_Disc_D3.0mm_W1.6mm_P2.50mm
C12: 10uF; CP_Radial_D5.0mm_P2.50mm
C13: 10uF; CP_Radial_D5.0mm_P2.50mm; not fitted
C14: 47nF; C_Disc_D3.0mm_W1.6mm_P2.50mm
C15: 220uF; CP_Radial_D8.0mm_P3.80mm
D1: LED; LED_D3.0mm
D2: 1N914; D_DO-35_SOD27_P7.62mm_Horizontal
H1, H2, H3, H4: MountingHole; MountingHole_3.2mm_M3
J1: AudioJack2; Jack_3.5mm_CUI_SJ1-3525N_Horizontal
J2: Conn_01x03; PinHeader_1x03_P2.54mm_Vertical; not fitted
LFO_Mod_Depth1: 100K; Potentiometer_Bourns_PTV09A-1_Single_Vertical
LFO_Rate1: 1M; Potentiometer_Bourns_PTV09A-1_Single_Vertical
LFO_SHAPING1, LFO_SHAPING2: SW_SPDT; ToggleSwitch_MTS-102_SPDT
LS1: Speaker; Speaker 2030
PWR1: SW_SPDT; ToggleSwitch_MTS-102_SPDT
Q1, Q2: 2N3904; TO-92_HandSolder
Q3: 2N5457; TO-92_HandSolder
R1, R2, R4, R9, R15, R19: 100K; R_Axial_DIN0207_L6.3mm_D2.5mm_P7.62mm_Horizontal
R3: 3K; R_Axial_DIN0207_L6.3mm_D2.5mm_P7.62mm_Horizontal
R5, R6, R7, R20: 4.7K; R_Axial_DIN0207_L6.3mm_D2.5mm_P7.62mm_Horizontal
R8, R10: 75K; R_Axial_DIN0207_L6.3mm_D2.5mm_P7.62mm_Horizontal
R11: 2K; R_Axial_DIN0207_L6.3mm_D2.5mm_P7.62mm_Horizontal
R12: 220K; R_Axial_DIN0207_L6.3mm_D2.5mm_P7.62mm_Horizontal
R13, R16: 2M; R_Axial_DIN0207_L6.3mm_D2.5mm_P7.62mm_Horizontal
R14, R17, R18, R22: 10K; R_Axial_DIN0207_L6.3mm_D2.5mm_P7.62mm_Horizontal
R21: 300K; R_Axial_DIN0207_L6.3mm_D2.5mm_P7.62mm_Horizontal
R23: 15K; R_Axial_DIN0207_L6.3mm_D2.5mm_P7.62mm_Horizontal
R24: 10R; R_Axial_DIN0207_L6.3mm_D2.5mm_P7.62mm_Horizontal
SYNC1: SW_SPDT; ToggleSwitch_MTS-102_SPDT
U1: LM324; DIP-14_W7.62mm_Socket_LongPads
U2: LM386; DIP-8_W7.62mm_Socket_LongPads
VCO_Freq1: 100K; Potentiometer_Bourns_PTV09A-1_Single_Vertical
Volume1: 100K; Potentiometer_Bourns_PTV09A-1_Single_Vertical

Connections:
B+: BT1.1 (+), PWR1.1 (A)
BN: BT1.2 (-), C1.2, C2.2, C4.2, C6.2, C11.1, C12.2, D1.1 (K), J2.3, LS1.2, R2.1, R7.1, R12.2, R15.1, R16.1, R20.1, R23.1, R24.1, U1.11 (V-), U2.2 (-), U2.4 (GND), VCO_Freq1.1, Volume1.3
BP: C2.1, C5.1, C11.2, J2.1, LFO_Mod_Depth1.3, PWR1.2 (B), R1.2, R6.2, R13.2, R22.2, U1.4 (V+), U2.6 (V+), VCO_Freq1.3
GND: C5.2, C6.1, J1.S, J2.2, LFO_Mod_Depth1.MP (MountPin), LFO_Rate1.MP (MountPin), Q2.2 (B), R6.1, R7.2, R11.2, U1.3 (+), U1.12 (+), VCO_Freq1.MP (MountPin), Volume1.MP (MountPin)
unnamed: C7.2, R14.2, U1.14
unnamed: C10.2, J1.R, J1.T
unnamed: C13.1, U2.1 (GAIN)
unnamed: C13.2, U2.8 (GAIN)
unnamed: C14.1, R24.2
unnamed: C14.2, C15.1, U2.5
unnamed: D2.2 (A), R21.1, U1.7
unnamed: D2.1 (K), R17.1
unnamed: J1.RN, J1.TN, R19.2
unnamed: C3.2, LFO_SHAPING1.2 (B), LFO_SHAPING2.1 (A)
unnamed: LFO_Mod_Depth1.1, LFO_SHAPING2.2 (B)
unnamed: Q1.2 (B), R9.1, R10.1, R11.1, R12.1
unnamed: C7.1, Q1.3 (C), R13.1, U1.13 (-)
unnamed: Q1.1 (E), Q2.1 (E), R14.1
unnamed: C9.1, Q2.3 (C), Q3.1 (D), U1.2 (-)
unnamed: Q3.3 (G), R16.2, R17.2
unnamed: C8.1, R15.2, SYNC1.2 (B)
unnamed: R18.1, R21.2, U1.5 (+)
unnamed: C8.2, R22.1, R23.2, U1.6 (-)
unnamed: R1.1, R2.2, R4.2, U1.10 (+)
unnamed: C1.1, R3.1, U1.9 (-)
unnamed: R19.1, R20.2, U2.3 (+)
unnamed: C12.1, U2.7 (BYPASS)
X1: LFO_Rate1.1, R3.2
X2: LFO_Mod_Depth1.2, R9.2
X3: C3.1, LFO_Rate1.2, LFO_Rate1.3, LFO_SHAPING1.1 (A), R4.1, R5.2, R8.2, SYNC1.1 (A), U1.8
X4: R10.2, VCO_Freq1.2
X5: C4.1, LFO_SHAPING2.3 (C), R8.1
X7: D1.2 (A), R5.1
X10: C15.2, LS1.1
X13: C10.1, Volume1.2
X14: C9.2, Q3.2 (S), R18.2, U1.1, Volume1.1

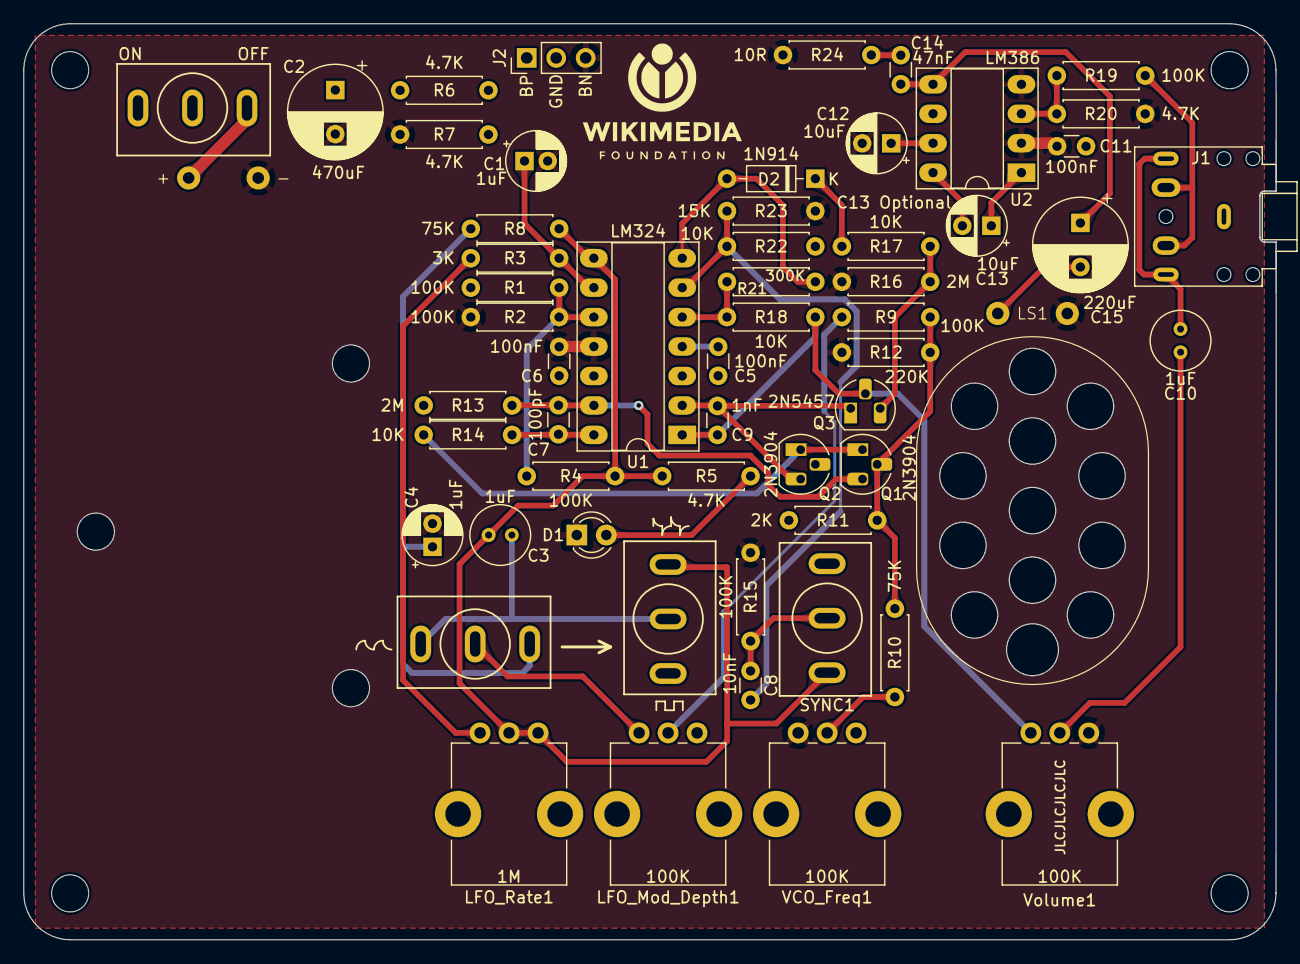
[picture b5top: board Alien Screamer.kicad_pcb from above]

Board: 4 copper layers, 108.0 x 79.0 mm, 62 parts (0 on the bottom side), 36 nets.
